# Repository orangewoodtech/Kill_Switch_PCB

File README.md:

# Kill_Switch_PCB

This Repo Contains all the Stuff related to the Kill Switch PCB : 

- Schematics ( .sch ) 
- Board ( .brd ) 
- Library (for KF part ) 
- Gerber File

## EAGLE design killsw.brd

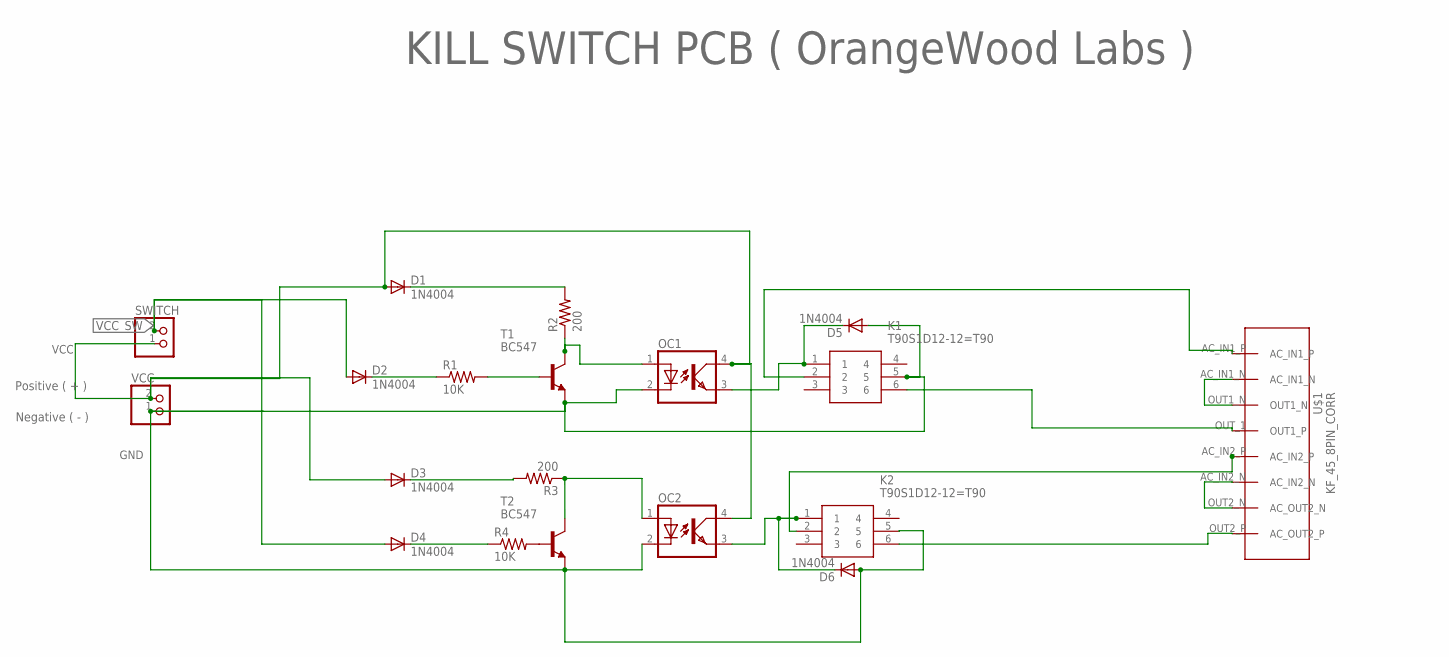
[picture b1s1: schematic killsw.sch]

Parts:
D1, D2, D3, D4, D5, D6: 1N4004; DO41-10
K1, K2: T90S1D12-12=T90
OC1, OC2: PC817; DIL04
R1, R4: 10K; 0204/7
R2, R3: 200; 0204/7
SWITCH: JST_2PIN-THM; JST-PH-2-THM
T1, T2: BC547; TO92
U$1: KF_45_8PIN_CORR; KF-45
VCC: JST_2PIN-THM; JST-PH-2-THM

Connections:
GND: D5.A, D6.A, K1.5, K2.5, OC1.2 (C), OC2.2 (C), T1.1 (E), T2.1 (E), VCC.1 (2)
unnamed: K1.2, U$1.AC_IN1_P
unnamed: D1.C, R2.2
unnamed: D2.C, R1.1
unnamed: D3.C, R3.2
unnamed: OC1.1 (A), R2.1, T1.3 (C)
unnamed: R1.2, T1.2 (B)
unnamed: K2.2, U$1.AC_IN2_P
unnamed: R4.2, T2.2 (B)
unnamed: D5.C, K1.1, OC1.3 (EMIT)
unnamed: K1.6, U$1.OUT_1 (OUT1_P)
unnamed: OC2.1 (A), R3.1, T2.3 (C)
unnamed: D4.C, R4.1
unnamed: D6.C, K2.1, OC2.3 (EMIT)
unnamed: K2.6, U$1.OUT2_P (AC_OUT2_P)
unnamed: U$1.AC_IN1_N, U$1.OUT1_N
unnamed: U$1.AC_IN2_N, U$1.OUT2_N (AC_OUT2_N)
VCC: D1.A, D3.A, OC1.4 (COL), OC2.4 (COL), SWITCH.1 (2), VCC.2 (1)
VCC_SW: D2.A, D4.A, SWITCH.2 (1)

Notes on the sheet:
Positive ( + )
Negative ( - )
KILL SWITCH PCB ( OrangeWood Labs )

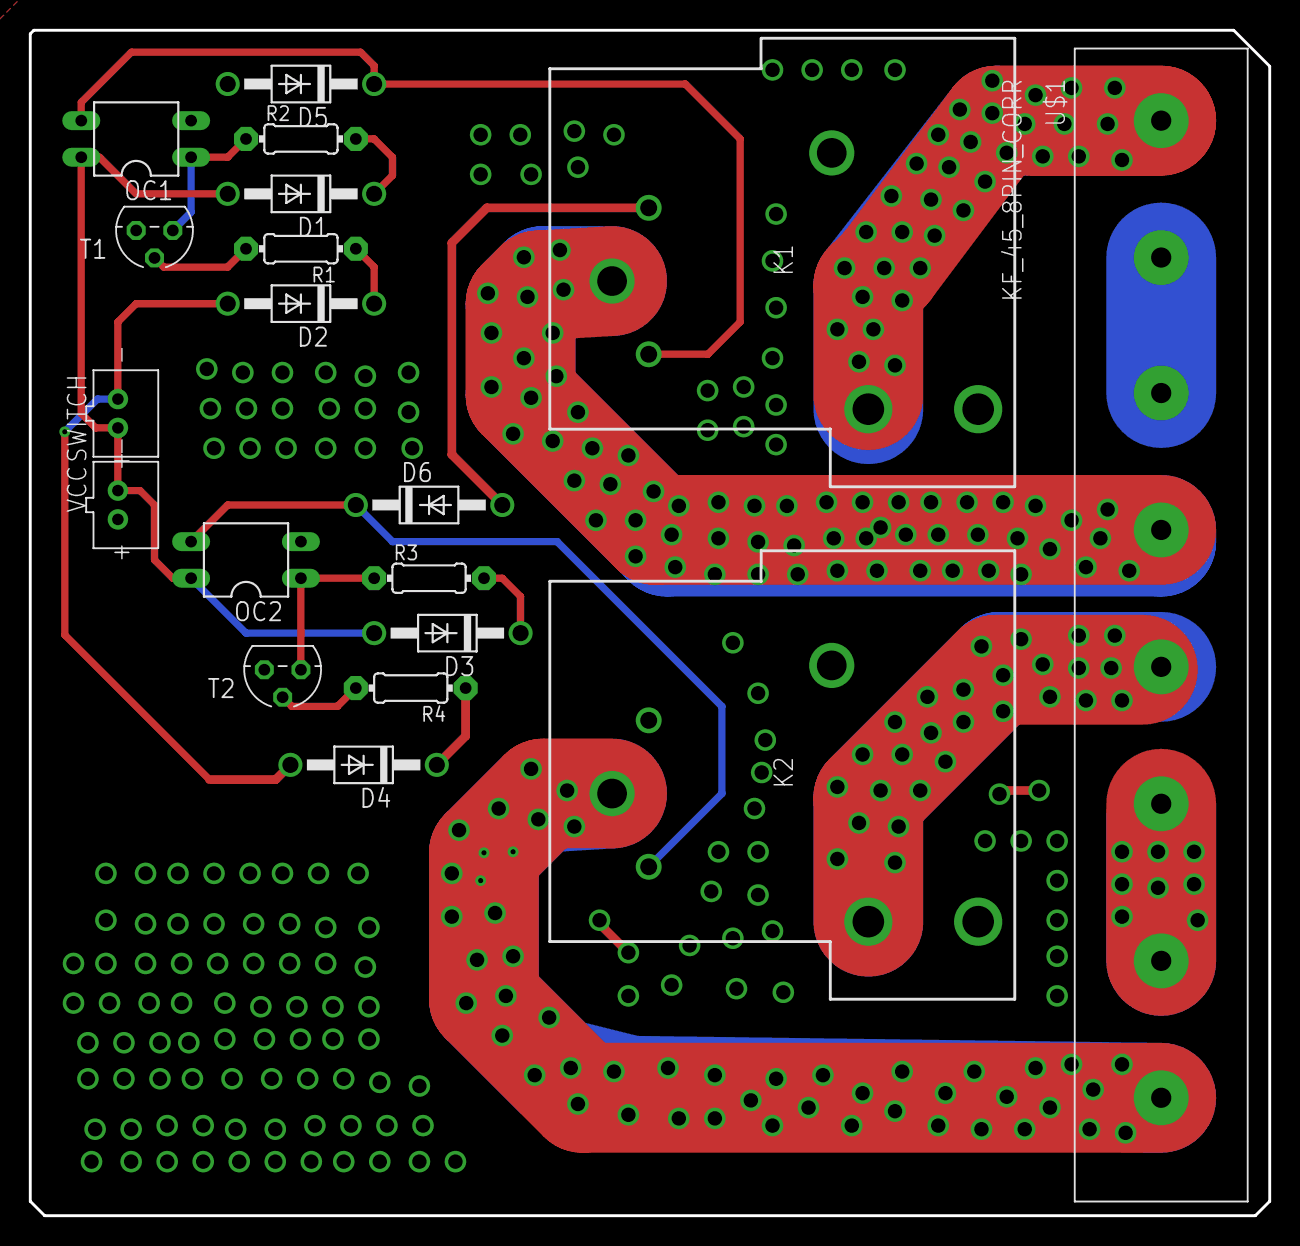
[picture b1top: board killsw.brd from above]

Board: 2 copper layers, 86.0 x 82.2 mm, 19 parts (0 on the bottom side), 19 nets.

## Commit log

2018-05-26 Add files via upload
    Eagle Library Built for the KF-85
